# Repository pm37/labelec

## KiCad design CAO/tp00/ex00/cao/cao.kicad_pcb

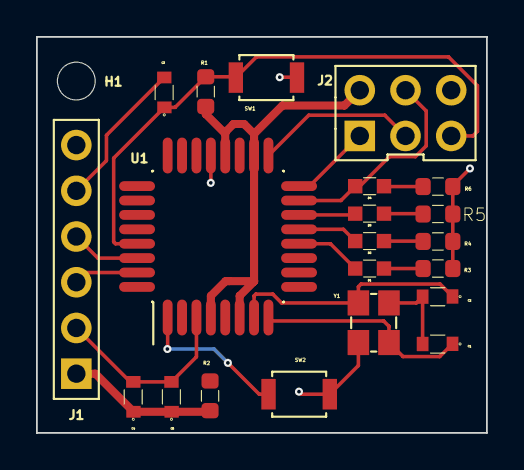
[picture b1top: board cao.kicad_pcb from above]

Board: 2 copper layers, 25.0 x 22.0 mm, 22 parts (0 on the bottom side), 20 nets.

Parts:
C1, C2: 22pF; C
C3: 100nF; C
C4, C5: 10uF; C
D1, D2, D3, D4: led; LED
H1: MoutingHole; MountingHole2.1mm
J1: Conn_01x06; PinHeaderMale2.54mm1x6
J2: AVR-ISP-6; PinHeaderMale2.54mm3x2
R1, R2: 10K; R_0603
R3, R4, R5, R6: 330R; R_0603
SW1, SW2: SW_Push; Btn
U1: ATmega328P-AU; atmega
Y1: 16MHz; crystal

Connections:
+5V: C4.1, C5.1, J1.1, J2.2, R1.2, R2.1, R2.2, U1.4, U1.6, U1.18, U1.20
/BUT_0: SW2.1, U1.1
/LED_0: D1.1, U1.12
/LED_1: D2.1, U1.13
/LED_2: D3.1, U1.14
/LED_3: D4.1, J2.4, U1.15
/MCU_RX: J1.4, U1.30
/MCU_TX: J1.3, U1.31
/MISO: J2.1, U1.16
/RESET: C3.1, J2.5, R1.1, SW1.1, U1.29
/SCK: J2.3, U1.17
GND: C4.2, C5.2, J1.2, J2.6, R3.2, R4.2, R5.2, R6.2, SW1.2, SW2.2, U1.3, U1.21, Y1.2
unnamed: C1.1, U1.8, Y1.3
unnamed: C1.2, C2.2, Y1.4
unnamed: C2.1, U1.7, Y1.1
unnamed: C3.2, J1.5
unnamed: D1.2, R3.1
unnamed: D2.2, R4.1
unnamed: D3.2, R5.1
unnamed: D4.2, R6.1
